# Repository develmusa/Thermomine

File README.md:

# Thermomine

**An aquarium decoration that tells you the water temperature from across the room.**

Thermomine is a 3D-printed naval mine that sits on the gravel of your tank. A sealed LED inside glows **blue** when the water is too cold, **green** when it's just right, and **red** when it's too warm. There's no display to squint at and no app: one look at the tank is enough.

> Product renders (Blender, Cycles). The product hasn't been photographed yet.

## How it works

| Glow | Water temperature (default range) | Meaning |
|---|---|---|
| 🔵 Blue | below 24 °C | too cold: check the heater |
| 🟢 Green | 24–27 °C | just right (tropical community tank) |
| 🔴 Red | above 27 °C | too warm: check for overheating |
| 🟣 Blinking purple | — | temperature probe not connected |

The colour fades smoothly over 1.5 °C at each limit. You can change the range in the firmware (`TEMP_LOW`, `TEMP_HIGH`).

- A stainless **DS18B20 probe** clips into the mine's base and measures the water.
- A sealed **WS2811 12 mm bullet pixel** (IP68) sits in a pocket inside the mine. Its light shines out through 16 slots in the band.
- The **controller board** stays dry outside the tank and is powered over USB-C.
- Both cables run over the tank rim with a drip loop, so water running down the cables drips off before it reaches the board.

## The mine

- **Size:** 155 mm tall, sphere Ø 80 mm, for 60–200 L tanks
- **Material:** MJF-printed PA12 nylon, black-dyed outside. A light-coloured interior reflects the LED and makes the glow brighter.
- **Two parts:** the bottom (base, tether, lower shell with glow slots) and the cap (top shell with horns)
- **Bayonet cap:** drop it on and turn it 30° clockwise until it clicks. It opens without tools for cleaning.
- **Flooded by design:** water fills the shell through the slots, and air escapes through 4 vents. Only the factory-sealed LED and probe get wet, so nothing printed has to be watertight.
- **Hollow base:** you fill it with sand for weight and seal it with aquarium silicone. That saves about 30 % of the print material.

<br clear="right">

| Inside: cable bore, LED pocket, glow slots | Hollow base for sand | Bayonet cap (open) |
|---|---|---|
|  |  |  |

## The controller board

- 58 × 42 mm, 2 layers, **designed for JLCPCB assembly**, so no soldering is needed
- **ESP32-C3-WROOM-02** with native USB, so USB-C goes straight to the chip with no USB-serial chip
- **AMS1117-3.3** regulator and a **74AHCT1G125** level shifter, which brings the LED data line to 5 V
- Two 5.08 mm **screw terminals:** LED (+5V / DIN / GND) and probe (GND / DQ / 3V3)
- **RESET** and **BOOT** buttons, and 4 × M3 mounting holes
- Generated in code with `pcb/build_board.py` (KiCad 10 + freerouting). The KiCad design-rule check passes with 0 errors.

<br clear="right">

## Getting one built

**1. Print the mine.** Upload [`print/mine_print_plate.3mf`](print/mine_print_plate.3mf) to an MJF print service (JLC3DP, Craftcloud, Sculpteo and so on) and choose PA12, black-dyed. STEP and STL versions are in the same folder. For assembly, sand filling and wiring, see [`print/README.md`](print/README.md).

**2. Order the board.** In [`pcb/fab/`](pcb/fab/) you'll find the Gerber zip, the BOM (with LCSC part numbers) and the CPL (component placement list). Upload all three to JLCPCB with PCB Assembly turned on. In their preview, check the rotation of U1, J1, U2 and U3, and confirm that part C474882 is the 3-pin terminal.

**3. Flash the firmware.** Open [`firmware/aquarium_mine_temp/aquarium_mine_temp.ino`](firmware/aquarium_mine_temp/aquarium_mine_temp.ino) in the Arduino IDE. Select "ESP32C3 Dev Module" and turn on "USB CDC On Boot". Install the OneWire, DallasTemperature and Adafruit NeoPixel libraries. For the first upload, hold BOOT while pressing RESET.

**Workshop drawings:** A3 part drawings to SN EN ISO conventions (first-angle projection, ISO 128 line types, ISO 129-1 dimensioning, ISO 2768-m). Click a preview to open the PDF:

| TM-001-01 Bottom part | TM-001-02 Cap |
|---|---|
|  |  |

**Parts to buy:** a 5 V WS2811 12 mm IP68 bullet pixel, a waterproof DS18B20 probe, a USB-C power supply and aquarium-safe silicone.

## Repository layout

| Folder | Contents |
|---|---|
| [`print/`](print/) | Print files (3MF, STEP, STL), the FreeCAD build scripts (`build_step.py`, `export_3mf.py`) and the assembly guide |
| [`pcb/`](pcb/) | KiCad board, generator script, fab files, 3D previews |
| [`firmware/`](firmware/) | Arduino sketch |
| [`marketing/`](marketing/) | Blender scenes, render scripts, product shots, TikTok concepts and clips |
| [`docs/images/`](docs/images/) | The images in this README |

## Marketing material

Concept first frames for TikTok, rendered in Blender with the exact print model, as bases for AI-generated video (MiniMax Hailuo). The target audience, positioning and listing copy are in [`marketing/README.md`](marketing/README.md).

## Status

This is a **prototype design**. Nothing has been built or tested yet:

- **Board and firmware:** designed and checked against the design rules, but not yet manufactured or run on hardware.
- **Print:** the files are valid, closed solids, but no part has been printed yet. Fit tolerances (0.3 mm bayonet clearance) may need adjusting after the first print.
- **Images:** all are renders, not photos. The glow brightness assumes a light-coloured interior.
- **Aquarium safety:** PA12 is generally considered inert in water but isn't certified for aquariums. Soak and rinse the parts before use.
- **Selling it:** in the EU this needs at least CE marking (EMC, RoHS). The ESP32 also brings the radio equipment rules into play, plus WEEE/ElektroG registration, LUCID packaging registration and the product safety regulation (GPSR). A version without a radio chip would make this simpler.

No license has been chosen yet.

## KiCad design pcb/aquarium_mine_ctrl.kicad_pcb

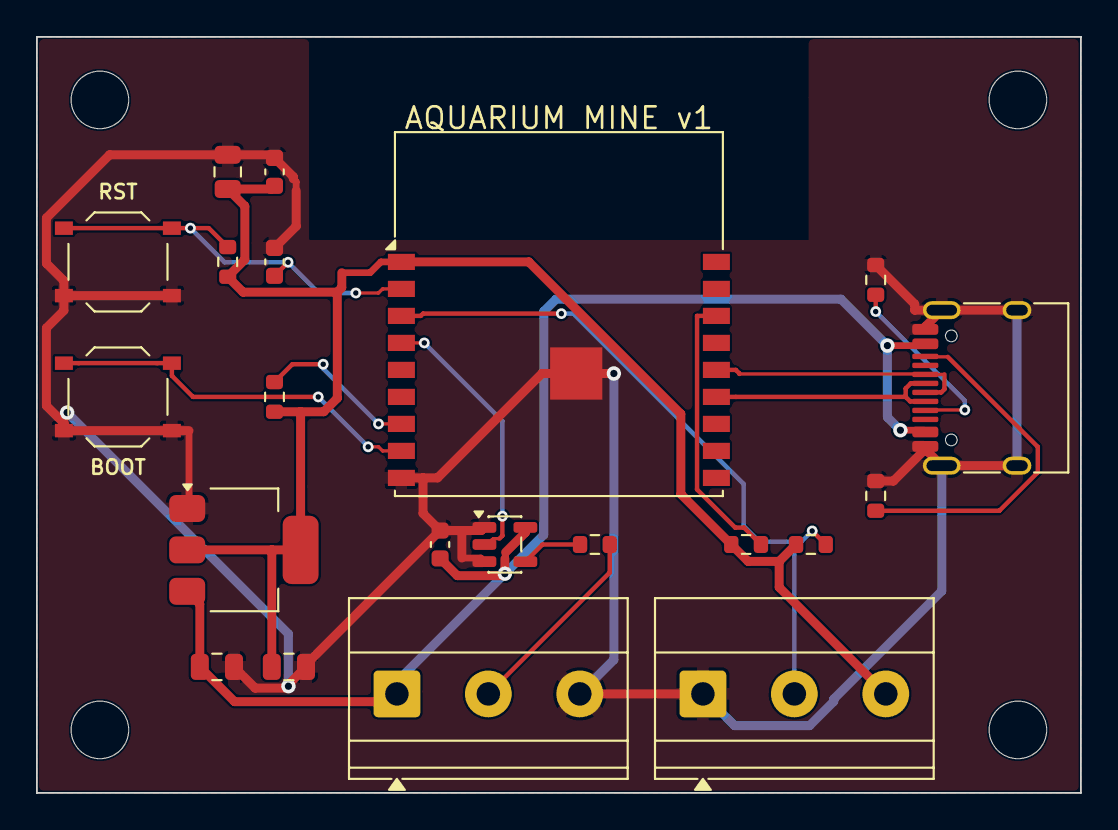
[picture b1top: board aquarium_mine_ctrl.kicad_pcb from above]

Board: 2 copper layers, 58.0 x 42.0 mm, 25 parts (0 on the bottom side), 15 nets.

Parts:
C1, C3: 10uF; C_0805_2012Metric
C2: 22uF; C_0805_2012Metric
C4, C6: 100nF; C_0603_1608Metric
C5: 1uF; C_0603_1608Metric
H1, H2, H3, H4: M3; MountingHole_3.2mm_M3
J1: USB-C; USB_C_Receptacle_HRO_TYPE-C-31-M-12
J2: LED +5V/DIN/GND; TerminalBlock_Phoenix_MKDS-1,5-3-5.08_1x03_P5.08mm_Horizont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
J3: PROBE GND/DQ/3V3; TerminalBlock_Phoenix_MKDS-1,5-3-5.08_1x03_P5.08mm_Horizont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
R1, R2, R3: 10k; R_0603_1608Metric
R4, R5: 5.1k; R_0603_1608Metric
R6: 4.7k; R_0603_1608Metric
R7: 330; R_0603_1608Metric
SW1: RESET; SW_Push_1P1T_XKB_TS-1187A
SW2: BOOT; SW_Push_1P1T_XKB_TS-1187A
U1: ESP32-C3-WROOM-02-N4; ESP32-C3-WROOM-02
U2: AMS1117-3.3; SOT-223-3_TabPin2
U3: 74AHCT1G125; SOT-23-5

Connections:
+3V3: C2.1, C3.1, C4.1, J3.3, R1.1, R2.1, R3.1, R6.1, U1.1, U2.2
CC1: J1.A5, R4.1
CC2: J1.B5, R5.1
EN: C5.1, R1.2, SW1.1, U1.2
GND: C1.2, C2.2, C3.2, C4.2, C5.2, C6.2, J1.A1, J1.A12, J1.B1, J1.B12, J1.SH, J2.3, J3.1, R4.2, R5.2, SW1.2, SW2.2, U1.9, U1.19, U2.1, U3.1, U3.3
IO2: R2.2, U1.16
IO8: R3.2, U1.7
IO9: SW2.1, U1.8
LED_3V3: U1.4, U3.2
LED_5V: R7.1, U3.4
LED_DIN: J2.2, R7.2
TEMP_DQ: J3.2, R6.2, U1.3
USB_DM: J1.A7, J1.B7, U1.13
USB_DP: J1.A6, J1.B6, U1.14
VBUS: C1.1, C6.1, J1.A4, J1.A9, J1.B4, J1.B9, J2.1, U2.3, U3.5

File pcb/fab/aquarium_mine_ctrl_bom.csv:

Comment,Designator,Footprint,Quantity,Manufacturer Part,LCSC Part #
ESP32-C3-WROOM-02-N4,U1,ESP32-C3-WROOM-02,1,ESP32-C3-WROOM-02-N4,C2934560
USB-C,J1,USB_C_Receptacle_HRO_TYPE-C-31-M-12,1,TYPE-C-31-M-12,C165948
AMS1117-3.3,U2,SOT-223-3_TabPin2,1,AMS1117-3.3,C6186
74AHCT1G125,U3,SOT-23-5,1,74AHCT1G125DBVTG4,C2870384
KF301-5.0-3P,"J2,J3","TerminalBlock_Phoenix_MKDS-1,5-3-5.08_1x03_P5.08mm_Horizontal",2,KF301-5.0-3P,C474882
TS-1187A-B-A-B,"SW1,SW2",SW_Push_1P1T_XKB_TS-1187A,2,TS-1187A-B-A-B,C318884
10uF,"C1,C3",C_0805_2012Metric,2,CL21A106KAYNNNE,C15850
22uF,C2,C_0805_2012Metric,1,CL21A226MAQNNNE,C45783
100nF,"C4,C6",C_0603_1608Metric,2,CC0603KRX7R9BB104,C14663
1uF,C5,C_0603_1608Metric,1,CL10A105KB8NNNC,C15849
10k,"R1,R2,R3",R_0603_1608Metric,3,0603WAF1002T5E,C25804
5.1k,"R4,R5",R_0603_1608Metric,2,0603WAF5101T5E,C23186
4.7k,R6,R_0603_1608Metric,1,0603WAF4701T5E,C23162
330,R7,R_0603_1608Metric,1,0603WAF3300T5E,C23138
